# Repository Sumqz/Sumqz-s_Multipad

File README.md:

# Sumqz-s_Multipad
My own custom Macropad. It's simple but includes a variety of features. It's supposed to make life with a 60% Keyboard better. To get the space benefit of the small Keyboard but they possibility to add extra buttons and features when needed. This project was made possible by blueprint.hackclub.

It's baisically a Macropad on steroids, while it may only have 6 buttons, it also includes a rotary encoder wich handles volume as well as 2 RGB LED's with diffrent LED patterns. Theres also a OLED wich displays the Session time to keep track of how long you've been using your PC.

I made this project by following the tutorial on https://blueprint.hackclub.com/ and added a few of my own ideas. It took about 12-14 hours of work since i had to get used to the new CAD programm. It was a whole lot of fun.

The Firmware is easely changeable to fit everyones needs. Once assembled it just needs to get flashed and it should work right away. 

Id;"Designator";"Footprint";"Quantity";"Designation";"Supplier and ref";					
1;"D2	D1";"LED_SK6812MINI_PLCC4_3.5x3.5mm_P1.75mm";2;"SK6812MINI";;;				
2;"SW9";"RotaryEncoder_Alps_EC11E-Switch_Vertical_H20mm";1;"RotaryEncoder_Switch";;;					
3;"SW2	SW5	SW6	SW1	SW3	SW4";"SW_Cherry_MX_1.00u_PCB";6;"SW_Push";;;
4;"U1";"XIAO-RP2040-DIP";1;"XIAO-RP2040-DIP";;;					
5;"J1";"FanPinHeader_1x04_P2.54mm_Vertical";1;"Conn_01x04";;;

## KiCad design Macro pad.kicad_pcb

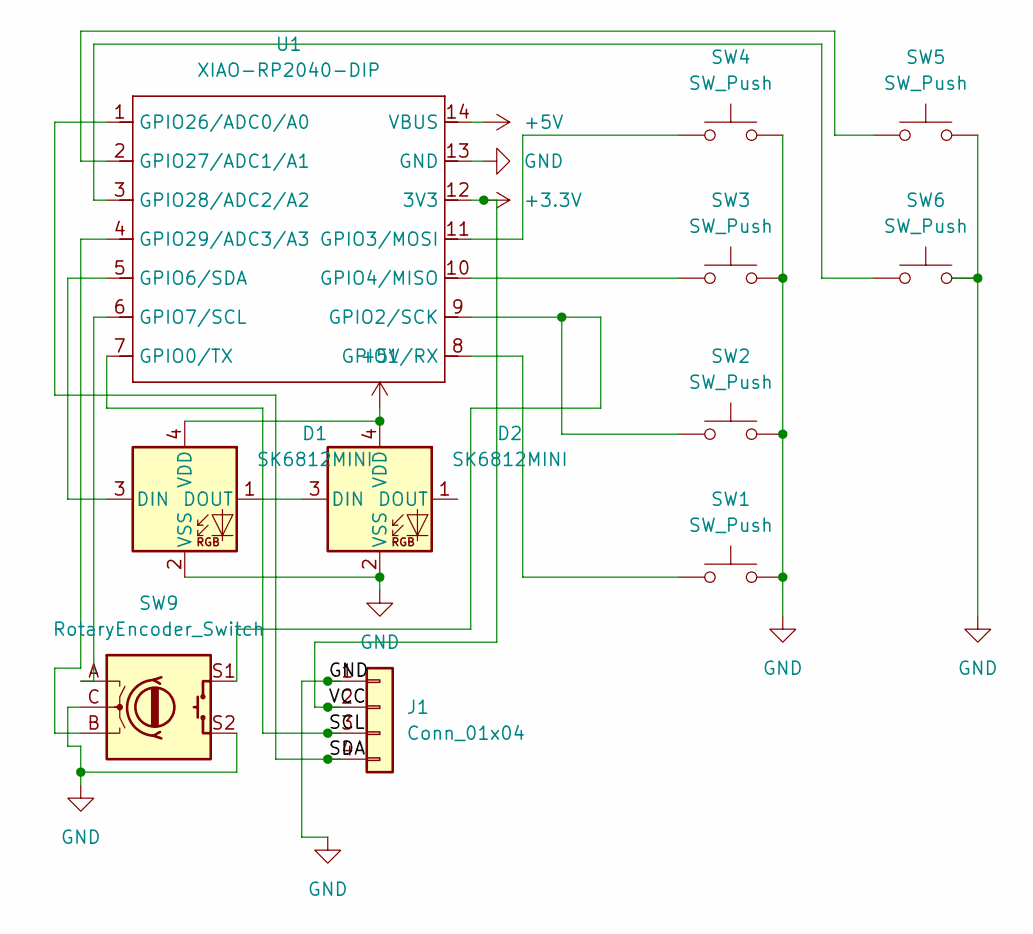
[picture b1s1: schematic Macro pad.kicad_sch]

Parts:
D1, D2: SK6812MINI; LED_SK6812MINI_PLCC4_3.5x3.5mm_P1.75mm
J1: Conn_01x04; FanPinHeader_1x04_P2.54mm_Vertical
SW1, SW2, SW3, SW4, SW5, SW6: SW_Push; SW_Cherry_MX_1.00u_PCB
SW9: RotaryEncoder_Switch; RotaryEncoder_Alps_EC11E-Switch_Vertical_H20mm
U1: XIAO-RP2040-DIP

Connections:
+3.3V: J1.2, U1.12 (3V3)
+5V: D1.4 (VDD), D2.4 (VDD), U1.14 (VBUS)
/SCL: J1.3, U1.7 (GPIO0/TX)
/SDA: J1.4, U1.1 (GPIO26/ADC0/A0)
GND: D1.2 (VSS), D2.2 (VSS), J1.1, SW1.2, SW2.2, SW3.2, SW4.2, SW5.2, SW6.2, SW9.C, SW9.S2, U1.13 (GND)
unnamed: D1.3 (DIN), U1.5 (GPIO6/SDA)
unnamed: D1.1 (DOUT), D2.3 (DIN)
unnamed: SW1.1, U1.8 (GPIO1/RX)
unnamed: SW2.1, SW9.S1, U1.9 (GPIO2/SCK)
unnamed: SW4.1, U1.11 (GPIO3/MOSI)
unnamed: SW3.1, U1.10 (GPIO4/MISO)
unnamed: SW9.A, U1.6 (GPIO7/SCL)
unnamed: SW5.1, U1.2 (GPIO27/ADC1/A1)
unnamed: SW6.1, U1.3 (GPIO28/ADC2/A2)
unnamed: SW9.B, U1.4 (GPIO29/ADC3/A3)

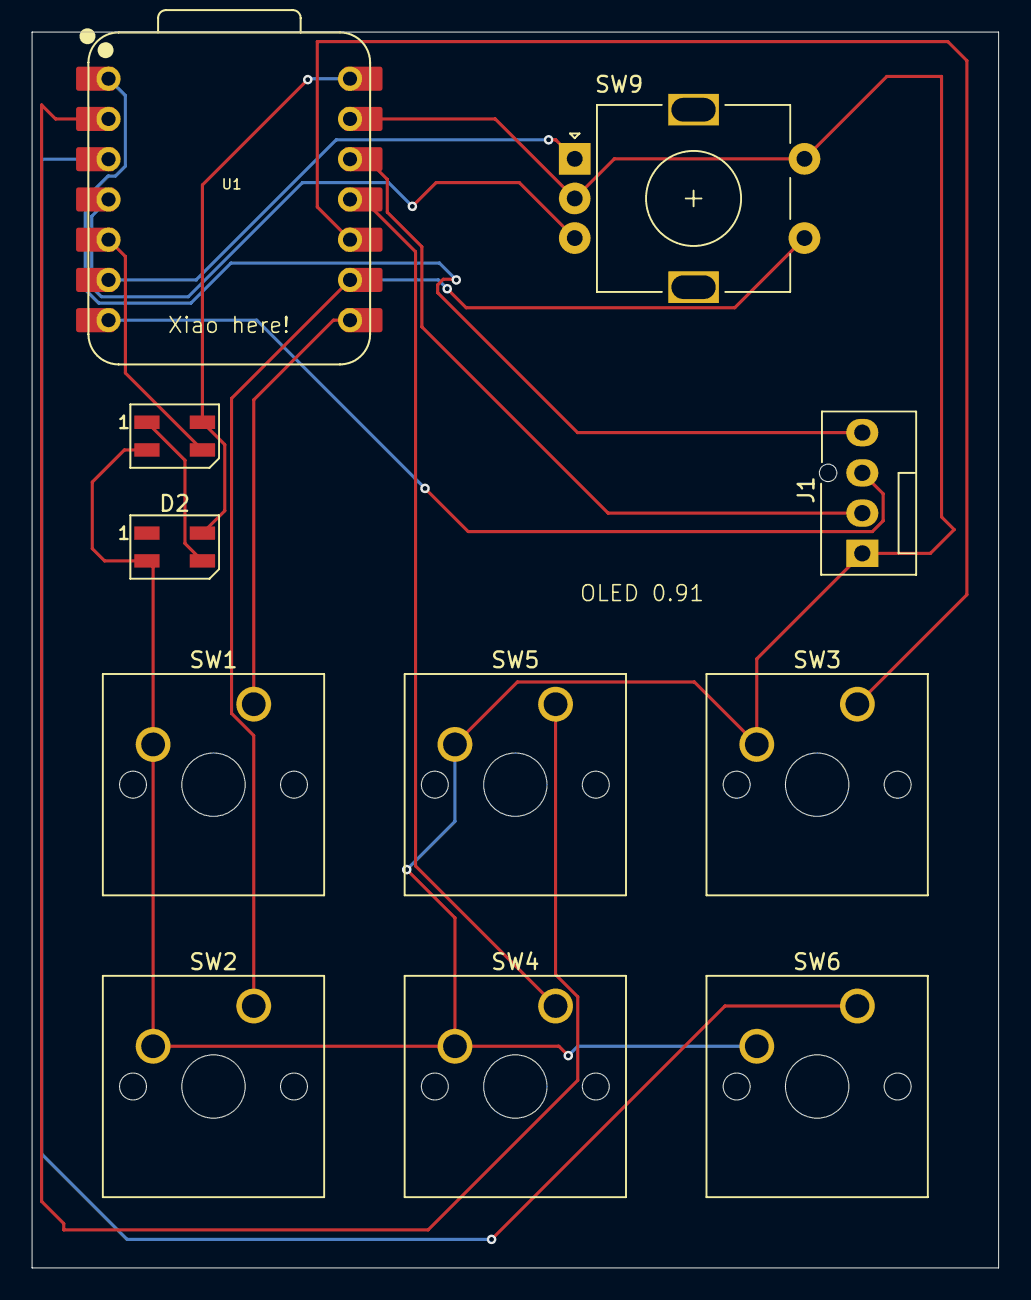
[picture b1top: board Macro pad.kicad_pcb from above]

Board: 2 copper layers, 61.0 x 78.0 mm, 11 parts (0 on the bottom side), 15 nets.

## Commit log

2026-02-04 Added the previously created files
2026-02-04 Added the firmware.
    I will soon add the features to the readme
2026-02-04 Added csv Bill
2026-02-04 Enhance README with project details and features
    Expanded project description and added details about features and assembly.
2026-02-04 Added 3d Model
